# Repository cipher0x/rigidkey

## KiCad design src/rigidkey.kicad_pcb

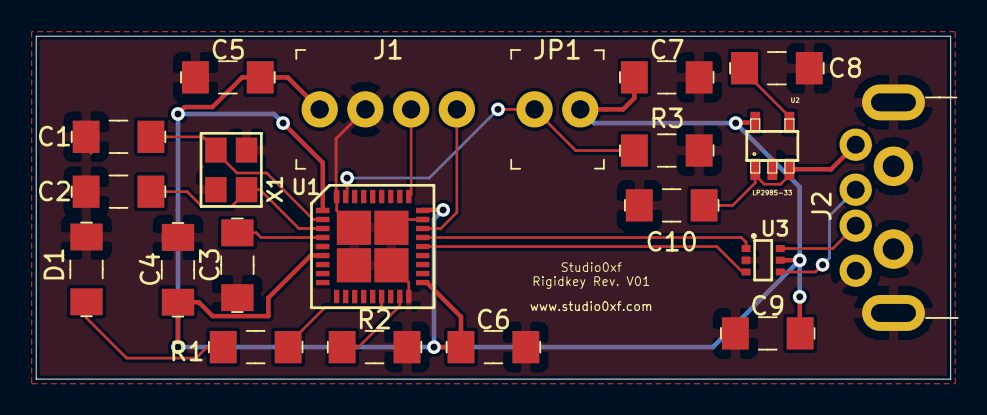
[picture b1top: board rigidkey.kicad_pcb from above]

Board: 2 copper layers, 50.8 x 19.0 mm, 21 parts (0 on the bottom side), 17 nets.

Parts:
C1, C2: 27pF; 1206
C3, C4, C5, C6, C7: 0.1uF; 1206
C8: 0.01uF; 1206
C9, C10: 4.7uF; 1206
D1: GREEN; 1206
J1: Conn_01x04_Male; PinHeader_1x4_P2.54mm_Drill1.02mm
J2: USB_A; USB_Male_A_UP2-AH-1-TH
JP1: Jumper; PinHeader_1x2_P2.54mm_Drill1.02mm
R1: R; 1206
R2, R3: 10k; 1206
U1: STM32F103TB; QFN36
U2: LP2985-33; SOT23-5
U3: NUF2221W1; SOT363
X1: 12MHz; ABM8G

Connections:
+3V3: C4.1, C5.2, C6.1, C7.2, C9.1, J1.1, JP1.2, U1.1, U1.6, U1.19, U1.27, U2.5, U3.5
/BOOTO: JP1.1, R3.1, U1.35
GND: C1.2, C2.1, C3.2, C4.2, C5.1, C6.2, C7.1, C8.2, C9.2, C10.2, D1.1, J1.2, J2.4, J2.5, R2.2, R3.2, U1.5, U1.18, U1.26, U1.36, U1.37, U2.2, U3.2, X1.3
unnamed: C1.1, U1.2, X1.1
unnamed: C2.2, U1.3, X1.2
unnamed: C3.1, U1.4
unnamed: C8.1, U2.4
unnamed: C10.1, J2.1, U2.1, U2.3
unnamed: D1.2, R1.2
unnamed: J1.3, U1.28
unnamed: J1.4, U1.25
unnamed: J2.2, U3.4
unnamed: J2.3, U3.6
unnamed: R1.1, U1.15
unnamed: R2.1, U1.17
unnamed: U1.23, U3.3
unnamed: U1.24, U3.1

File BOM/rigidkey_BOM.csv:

Id,Designator,Package,Quantity,Designation,Digi-Key Part Number,Manufacturer,Manufacturer Part Number,Temp Range
1,U1,QFN36,1,STM32F103TB,497-18523-ND,STI,STM32F103TBU7,-40°C ~ 105°C
2,"C9,C10",1206,2,4.7uF,399-3697-1-ND ,KEMET ,T491A475K016AT,-55°C ~ 125°C
3,"C6,C3,C4,C5,C7",1206,5,0.1uF,1276-1017-1-ND,Samsung Electro-Mechanics,CL31B104KBCNNNC,-55°C ~ 125°C
4,"C1,C2",1206,2,27pF,1276-2826-1-ND,Samsung Electro-Mechanics,CL31C270JBCNNNC,-55°C ~ 125°C
5,C8,1206,1,0.01uF,478-13075-1-ND , AVX Corporation,1206AC103KAT1A,-55°C ~ 125°C
6,D1,1206,1,GREEN,1080-1419-1-ND ,Everlight Electronics Co Ltd,QTLP650D4TR,?
7,J1,PinHeader_1x4_P2.54mm_Drill1.02mm,1,Conn_01x04_Male,609-3275-ND ,Amphenol ICC (FCI),68001-112HLF,?
8,J2,USB_Male_A_UP2-AH-1-TH,1,USB_A,102-5896-ND,,UP2-AH-4-TH ,
9,JP1,PinHeader_1x2_P2.54mm_Drill1.02mm,1,Jumper,,,,
10,R1,1206,1,500,PLT1206-500ATR-ND ,Vishay Thin Film,PLT1206-500ACT-ND ,-55°C ~ 155°C
11,"R2,R3",1206,2,10k,749-1550-1-ND,Vishay Beyschlag,MCA12060D1002BP500,-55°C ~ 125°C
12,U2,SOT23-5,1,LP2985-33, 296-18476-1-ND,Texas Instruments,LP2985-33DBVR, -40°C ~ 125°C
13,U3,SOT363,1,NUF2221W1,NUF2221W1T2GOSCT-ND ,ON Semiconductor,NUF2221W1T2G,-55°C ~ 125°C
14,X1,ABM8G,1,12MHz,535-10901-1-ND ,Abracon LLC,ABM8G-12.000MHZ-4Y-T3 ,-10°C ~ 60°C

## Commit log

2019-08-03 init
2019-08-03 Create net list
2019-08-04 Layout board
2019-08-05 Add BOM
2019-08-05 Generate gerbers
2019-08-16 add to do list

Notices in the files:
src/rigidkey.kicad_pcb:
License: CC By 4.0
